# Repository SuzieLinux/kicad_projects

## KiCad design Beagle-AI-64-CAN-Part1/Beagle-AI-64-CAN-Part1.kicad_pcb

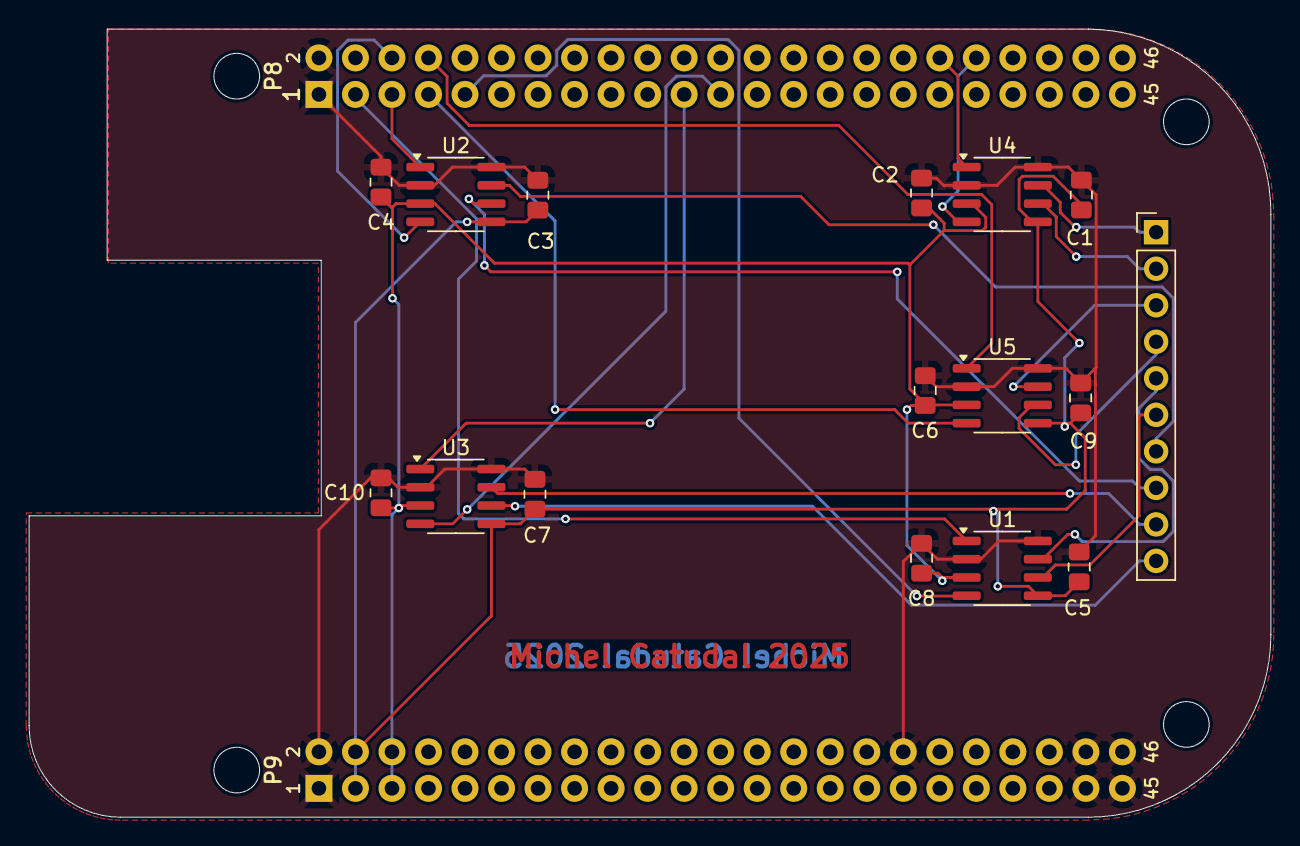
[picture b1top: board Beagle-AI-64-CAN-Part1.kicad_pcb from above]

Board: 2 copper layers, 86.4 x 54.8 mm, 17 parts (0 on the bottom side), 23 nets.

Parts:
C1, C2, C3, C4, C5, C6, C7, C8, C9, C10: 0.1uF; C_0805_2012Metric_Pad1.18x1.45mm_HandSolder
J17: Beaglebone_AI64; BEAGLE_BONE_BLACK_CAPE
P1: CAN group; PinHeader_1x10_P2.54mm_Vertical
U1, U2, U3, U4, U5: MCP2562; SOIC-8_3.9x4.9mm_P1.27mm

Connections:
+3.3V: C1.2, C3.2, C5.2, C7.2, C9.2, J17.P9.3 (VSYS_IO_3V3), J17.P9.4 (VSYS_IO_3V3), U1.5 (Vio), U2.5 (Vio), U3.5 (Vio), U4.5 (Vio), U5.5 (Vio)
+5V: C2.1, C4.1, C6.1, C8.1, C10.1, J17.P9.5 (DC_VDD_5V), J17.P9.6 (DC_VDD_5V), U1.3 (VDD), U2.3 (VDD), U3.3 (VDD), U4.3 (VDD), U5.3 (VDD)
/CAN4H: P1.1, U4.7 (CANH)
/CAN4L: P1.2, U4.6 (CANL)
/CAN5H: P1.3, U5.7 (CANH)
/CAN5L: P1.4, U5.6 (CANL)
/CAN6H: P1.5, U1.7 (CANH)
/CAN6L: P1.6, U1.6 (CANL)
/CAN7H: P1.7, U2.7 (CANH)
/CAN7L: P1.8, U2.6 (CANL)
/CAN8H: P1.9, U3.7 (CANH)
/CAN8L: P1.10, U3.6 (CANL)
GND: C1.1, C2.2, C3.1, C4.2, C5.1, C6.2, C7.1, C8.2, C9.1, C10.2, J17.P8.1 (GND), J17.P8.2 (GND), J17.P9.1 (GND), J17.P9.2 (GND), J17.P9.34 (GND), J17.P9.43 (GND), J17.P9.44 (GND), J17.P9.45 (GND), J17.P9.46 (GND), U1.2 (VSS), U1.8 (STBY), U2.2 (VSS), U2.8 (STBY), U3.2 (VSS), U3.8 (STBY), U4.2 (VSS), U4.8 (STBY), U5.2 (VSS), U5.8 (STBY)
unnamed: J17.P8.23 (AB23_MCAN8_RX), U3.4 (RXD)
unnamed: J17.P8.7 (AD24_MCAN5_RX), U5.4 (RXD)
unnamed: J17.P8.36 (AE20_MCAN4_TX), U4.1 (TXD)
unnamed: J17.P8.9 (AE24_MCAN6_RX), U1.4 (RXD)
unnamed: J17.P8.21 (AF21_MCAN8_TX), U3.1 (TXD)
unnamed: J17.P8.8 (AG24_MCAN5_TX), U5.1 (TXD)
unnamed: J17.P8.6 (AG25_MCAN7_RX), U2.4 (RXD)
unnamed: J17.P8.3 (AH21_MCAN6_TX), U1.1 (TXD)
unnamed: J17.P8.5 (AH25_MCAN7_TX), U2.1 (TXD)
unnamed: J17.P8.38 (Y29_AJ20), U4.4 (RXD)

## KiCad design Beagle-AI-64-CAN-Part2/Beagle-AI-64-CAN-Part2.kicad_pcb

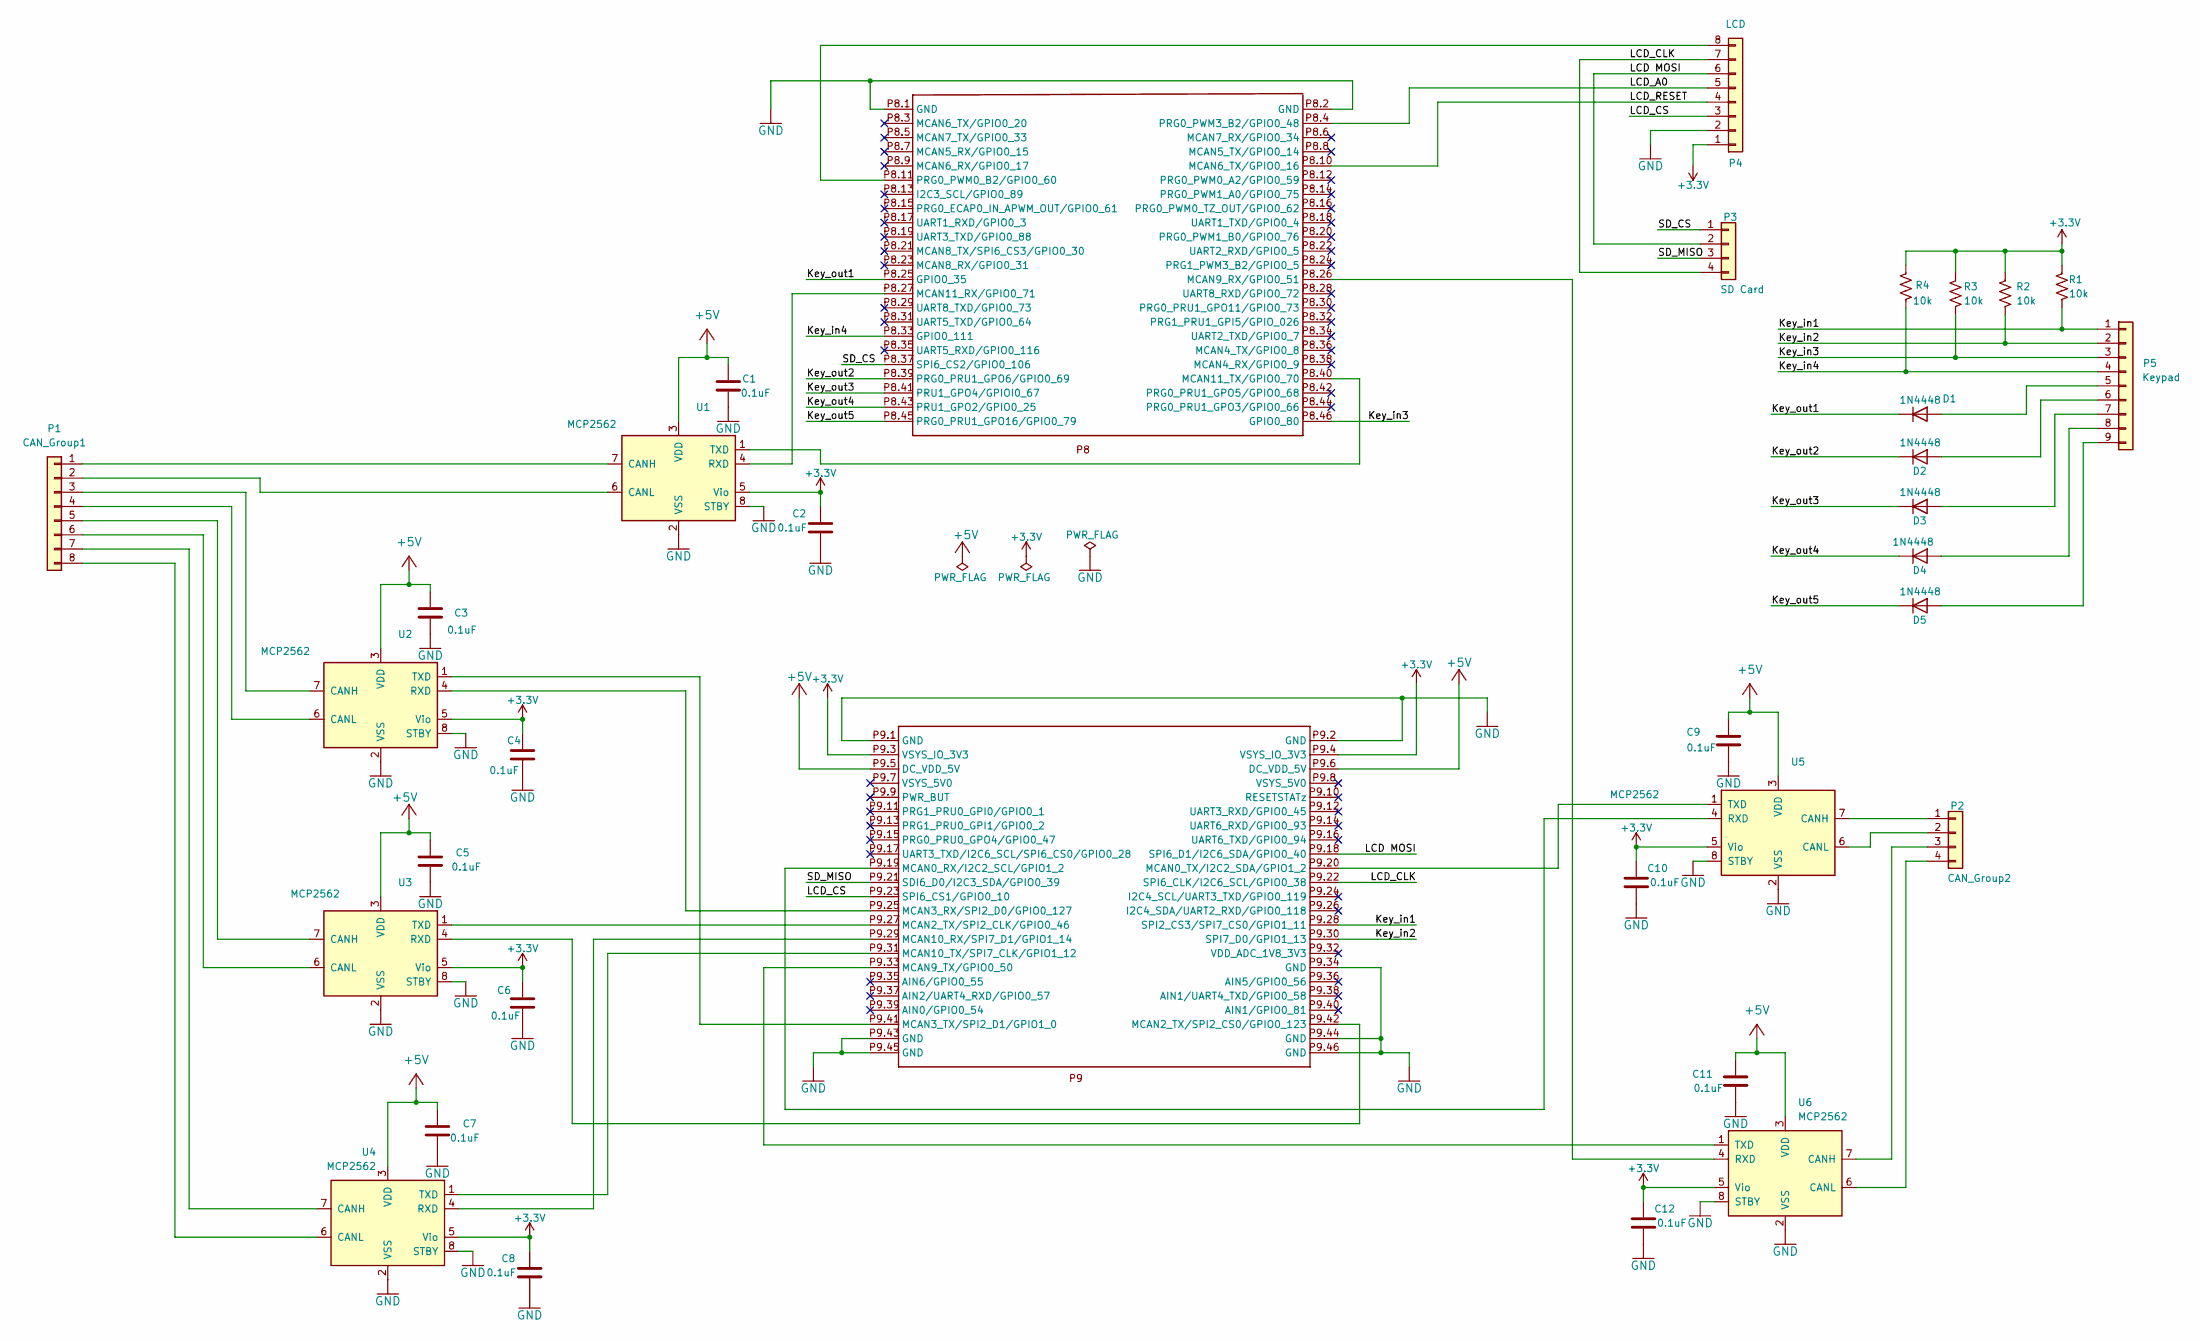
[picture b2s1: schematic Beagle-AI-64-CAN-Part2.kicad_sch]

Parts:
C1, C2, C3, C4, C5, C6, C7, C8, C9, C10, C11, C12: 0.1uF; C_0805_2012Metric_Pad1.18x1.45mm_HandSolder
D1, D2, D3, D4, D5: 1N4448; D_DO-35_SOD27_P7.62mm_Horizontal
J17: Beaglebone_AI64; BEAGLE_BONE_BLACK_CAPE
P1: CAN_Group1; PinHeader_1x08_P2.54mm_Vertical
P2: CAN_Group2; PinHeader_1x04_P2.54mm_Vertical
P3: SD Card; PinHeader_1x04_P2.54mm_Vertical
P4: LCD; PinHeader_1x08_P2.54mm_Vertical
P5: Keypad; PinHeader_1x09_P2.54mm_Vertical
R1, R2, R3, R4: 10k; R_0805_2012Metric
U1, U2, U3, U4, U5, U6: MCP2562; SOIC-8_3.9x4.9mm_P1.27mm

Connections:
+3.3V: C2.2, C4.2, C6.2, C8.2, C10.2, C12.2, J17.P9.3 (VSYS_IO_3V3), J17.P9.4 (VSYS_IO_3V3), P4.1, R1.1, R2.1, R3.1, R4.1, U1.5 (Vio), U2.5 (Vio), U3.5 (Vio), U4.5 (Vio), U5.5 (Vio), U6.5 (Vio)
+5V: C1.1, C3.1, C5.1, C7.1, C9.1, C11.1, J17.P9.5 (DC_VDD_5V), J17.P9.6 (DC_VDD_5V), U1.3 (VDD), U2.3 (VDD), U3.3 (VDD), U4.3 (VDD), U5.3 (VDD), U6.3 (VDD)
/Key_in1: J17.P9.28 (SPI2_CS3/SPI7_CS0/GPIO1_11), P5.1, R1.2
/Key_in2: J17.P9.30 (SPI7_D0/GPIO1_13), P5.2, R2.2
/Key_in3: J17.P8.46 (GPIO0_80), P5.3, R3.2
/Key_in4: J17.P8.33 (GPIO0_111), P5.4, R4.2
/Key_out1: D1.1 (K), J17.P8.25 (GPIO0_35)
/Key_out2: D2.1 (K), J17.P8.39 (PRG0_PRU1_GPO6/GPIO0_69)
/Key_out3: D3.1 (K), J17.P8.41 (PRU1_GPO4/GPIOI0_67)
/Key_out4: D4.1 (K), J17.P8.43 (PRU1_GPO2/GPIO0_25)
/Key_out5: D5.1 (K), J17.P8.45 (PRG0_PRU1_GPO16/GPIO0_79)
/LCD MOSI: J17.P9.18 (SPI6_D1/I2C6_SDA/GPIO0_40), P3.2, P4.6
/LCD_A0: J17.P8.4 (PRG0_PWM3_B2/GPIO0_48), P4.5
/LCD_CLK: J17.P9.22 (SPI6_CLK/I2C6_SCL/GPIO0_38), P3.4, P4.7
/LCD_CS: J17.P9.23 (SPI6_CS1/GPIO0_10), P4.3
/LCD_RESET: J17.P8.10 (MCAN6_TX/GPIO0_16), P4.4
/SD_CS: J17.P8.37 (SPI6_CS2/GPIO0_106), P3.1
/SD_MISO: J17.P9.21 (SDI6_D0/I2C3_SDA/GPIO0_39), P3.3
GND: C1.2, C2.1, C3.2, C4.1, C5.2, C6.1, C7.2, C8.1, C9.2, C10.1, C11.2, C12.1, J17.P8.1 (GND), J17.P8.2 (GND), J17.P9.1 (GND), J17.P9.2 (GND), J17.P9.34 (GND), J17.P9.43 (GND), J17.P9.44 (GND), J17.P9.45 (GND), J17.P9.46 (GND), P4.2, U1.2 (VSS), U1.8 (STBY), U2.2 (VSS), U2.8 (STBY), U3.2 (VSS), U3.8 (STBY), U4.2 (VSS), U4.8 (STBY), U5.2 (VSS), U5.8 (STBY), U6.2 (VSS), U6.8 (STBY)
unnamed: D1.2 (A), P5.5
unnamed: D2.2 (A), P5.6
unnamed: D3.2 (A), P5.7
unnamed: D4.2 (A), P5.8
unnamed: D5.2 (A), P5.9
unnamed: J17.P8.26 (MCAN9_RX/GPIO0_51), U6.4 (RXD)
unnamed: J17.P8.27 (MCAN11_RX/GPIO0_71), U1.4 (RXD)
unnamed: J17.P8.40 (MCAN11_TX/GPIO0_70), U1.1 (TXD)
unnamed: J17.P8.11 (PRG0_PWM0_B2/GPIO0_60), P4.8
unnamed: J17.P9.19 (MCAN0_RX/I2C2_SCL/GPIO1_2), U5.4 (RXD)
unnamed: J17.P9.20 (MCAN0_TX/I2C2_SDA/GPIO1_2), U5.1 (TXD)
unnamed: J17.P9.27 (MCAN2_TX/SPI2_CLK/GPIO0_46), U3.1 (TXD)
unnamed: J17.P9.42 (MCAN2_TX/SPI2_CS0/GPIO0_123), U3.4 (RXD)
unnamed: J17.P9.25 (MCAN3_RX/SPI2_D0/GPIO0_127), U2.4 (RXD)
unnamed: J17.P9.41 (MCAN3_TX/SPI2_D1/GPIO1_0), U2.1 (TXD)
unnamed: J17.P9.33 (MCAN9_TX/GPIO0_50), U6.1 (TXD)
unnamed: J17.P9.29 (MCAN10_RX/SPI7_D1/GPIO1_14), U4.4 (RXD)
unnamed: J17.P9.31 (MCAN10_TX/SPI7_CLK/GPIO1_12), U4.1 (TXD)
unnamed: P1.1, U1.7 (CANH)
unnamed: P1.2, U1.6 (CANL)
unnamed: P1.3, U2.7 (CANH)
unnamed: P1.4, U2.6 (CANL)
unnamed: P1.5, U3.7 (CANH)
unnamed: P1.6, U3.6 (CANL)
unnamed: P1.7, U4.7 (CANH)
unnamed: P1.8, U4.6 (CANL)
unnamed: P2.1, U5.7 (CANH)
unnamed: P2.2, U5.6 (CANL)
unnamed: P2.3, U6.7 (CANH)
unnamed: P2.4, U6.6 (CANL)

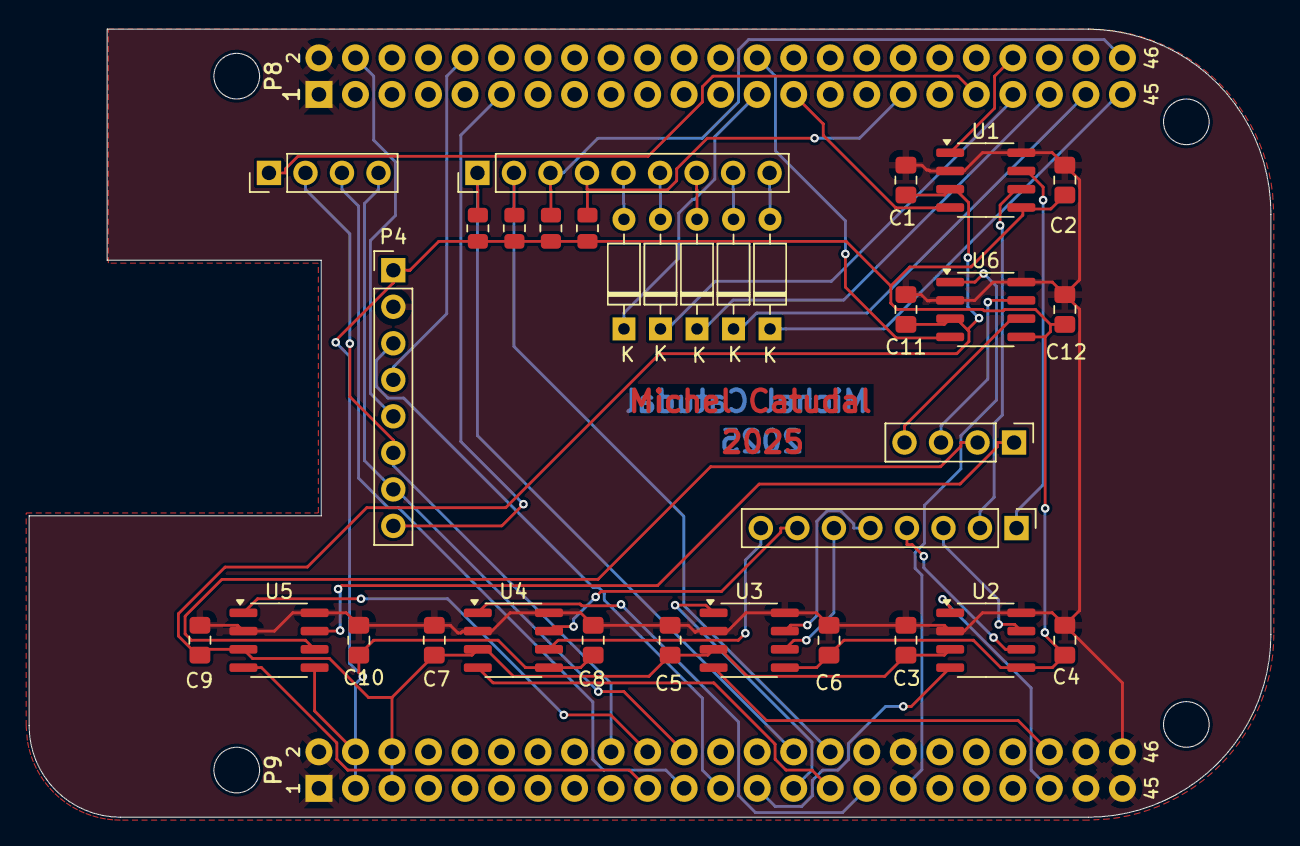
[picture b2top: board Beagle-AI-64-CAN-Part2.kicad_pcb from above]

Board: 2 copper layers, 86.4 x 54.8 mm, 33 parts (0 on the bottom side), 49 nets.

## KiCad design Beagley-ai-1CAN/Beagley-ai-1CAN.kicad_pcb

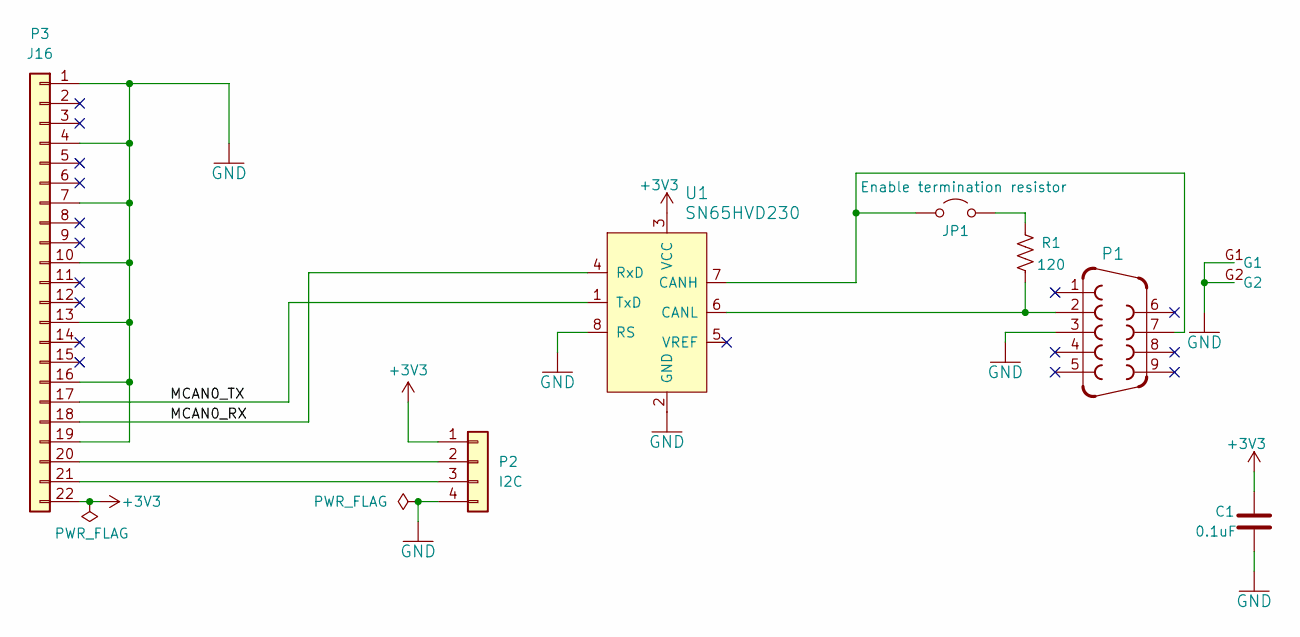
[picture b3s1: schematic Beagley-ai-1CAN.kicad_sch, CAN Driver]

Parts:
C1: 0.1uF; C_0805_2012Metric_Pad1.18x1.45mm_HandSolder
JP1: Enable termination resistor; PinHeader_1x02_P2.54mm_Vertical
P1: F09HP
P2: I2C; PinHeader_1x04_P2.00mm_Vertical
P3: J16; PinHeader_2x11_P2.54mm_reverse
R1: 120; R_2512_6332Metric_Pad1.40x3.35mm_HandSolder
U1: SN65HVD230; SOIC-8_3.9x4.9mm_P1.27mm; MPN SN65HVD230

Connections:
+3V3: C1.1, P2.1, P3.22, U1.3 (VCC)
/MCAN0_RX: P3.18, U1.4 (RxD)
/MCAN0_TX: P3.17, U1.1 (TxD)
GND: C1.2, P1.3, P1.G1, P1.G2, P2.4, P3.1, P3.4, P3.7, P3.10, P3.13, P3.16, P3.19, U1.2 (GND), U1.8 (RS)
unnamed: JP1.1 (A), P1.7, U1.7 (CANH)
unnamed: JP1.2 (B), R1.1
unnamed: P2.2, P3.20
unnamed: P2.3, P3.21
unnamed: P1.2, R1.2, U1.6 (CANL)

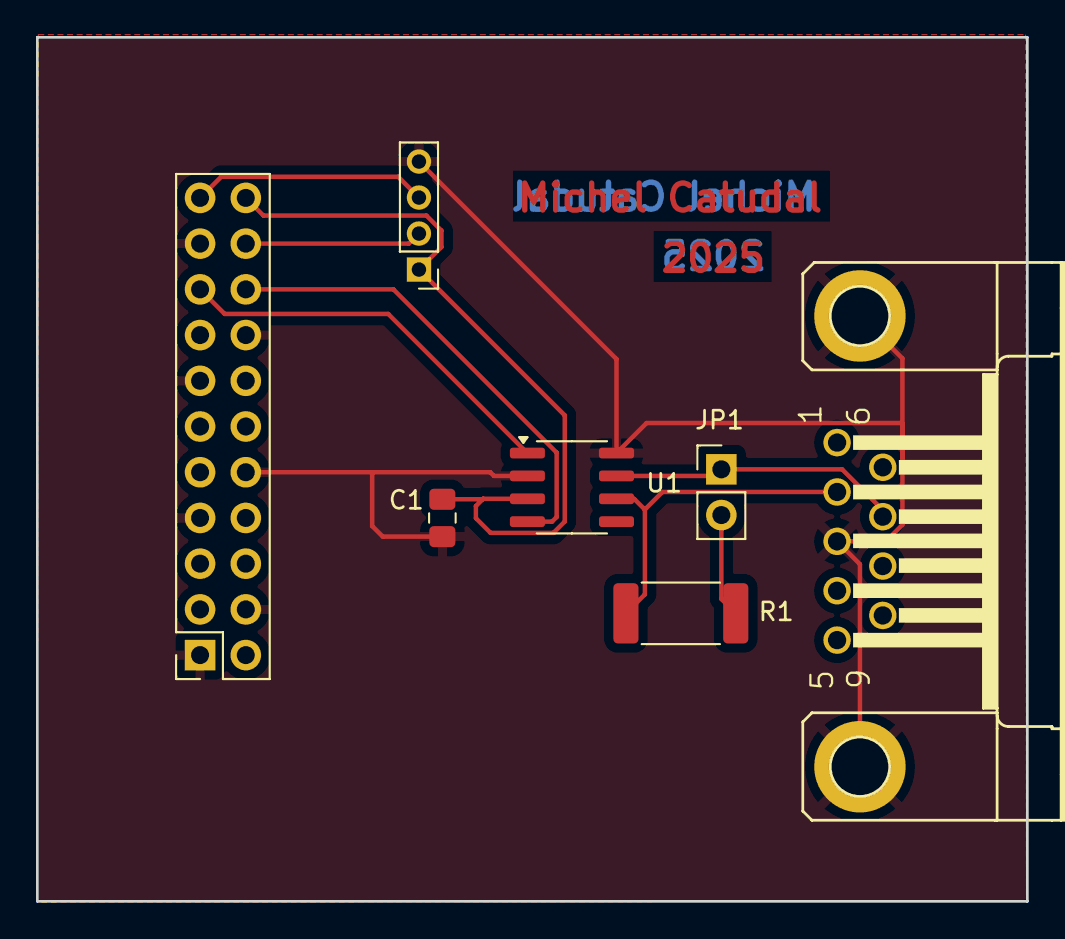
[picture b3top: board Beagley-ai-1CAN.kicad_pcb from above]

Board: 2 copper layers, 55.0 x 48.0 mm, 7 parts (0 on the bottom side), 9 nets.

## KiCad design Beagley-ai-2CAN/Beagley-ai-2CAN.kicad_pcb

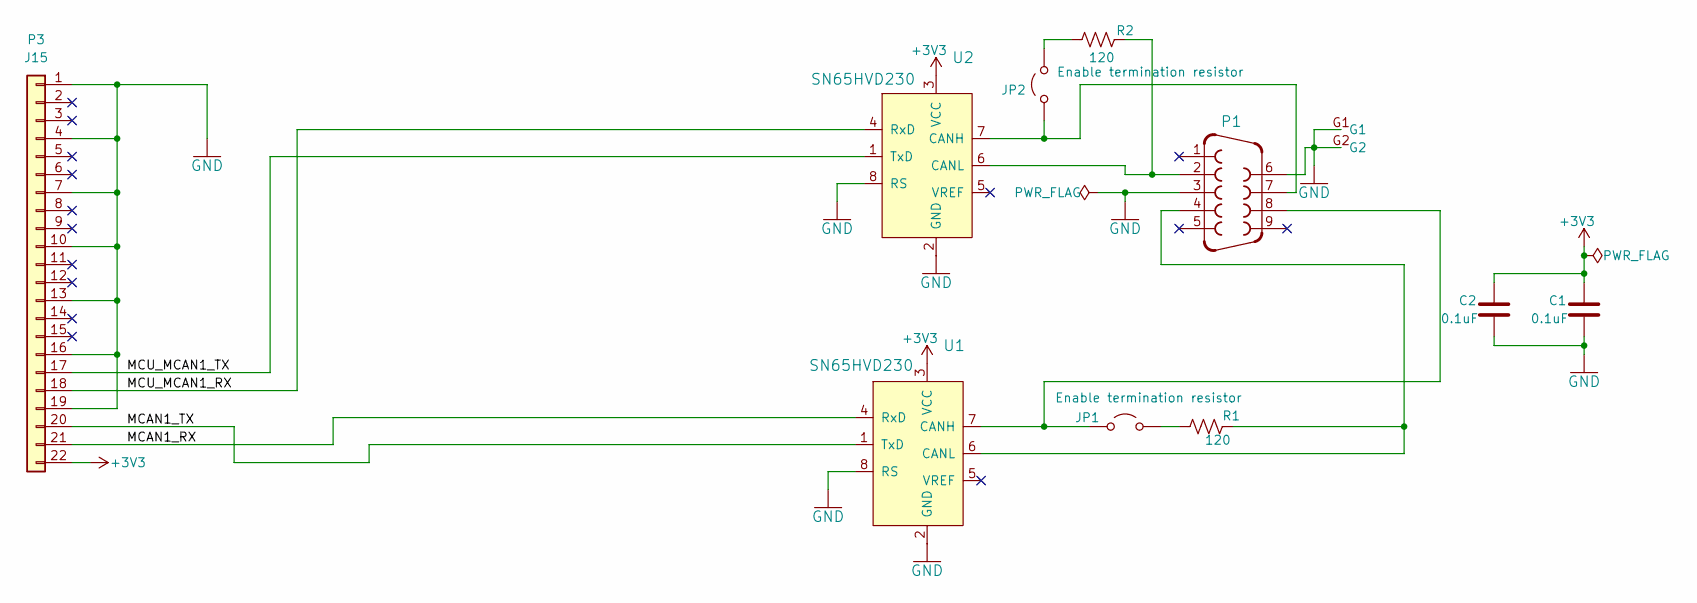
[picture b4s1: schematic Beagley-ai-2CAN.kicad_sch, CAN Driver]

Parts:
C1, C2: 0.1uF; C_0805_2012Metric_Pad1.18x1.45mm_HandSolder
JP1, JP2: Enable termination resistor; PinHeader_1x02_P2.54mm_Vertical
P1: F09HP
P3: J15; PinHeader_2x11_P2.54mm_reverse
R1, R2: 120; R_2512_6332Metric_Pad1.40x3.35mm_HandSolder
U1, U2: SN65HVD230; SOIC-8_3.9x4.9mm_P1.27mm; MPN SN65HVD230

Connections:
+3V3: C1.1, C2.1, P3.22, U1.3 (VCC), U2.3 (VCC)
/MCAN1_RX: P3.21, U1.4 (RxD)
/MCAN1_TX: P3.20, U1.1 (TxD)
/MCU_MCAN1_RX: P3.18, U2.4 (RxD)
/MCU_MCAN1_TX: P3.17, U2.1 (TxD)
GND: C1.2, C2.2, P1.3, P1.6, P1.G1, P1.G2, P3.1, P3.4, P3.7, P3.10, P3.13, P3.16, P3.19, U1.2 (GND), U1.8 (RS), U2.2 (GND), U2.8 (RS)
unnamed: JP1.1 (A), P1.8, U1.7 (CANH)
unnamed: JP1.2 (B), R1.1
unnamed: JP2.1 (A), P1.7, U2.7 (CANH)
unnamed: JP2.2 (B), R2.1
unnamed: P1.4, R1.2, U1.6 (CANL)
unnamed: P1.2, R2.2, U2.6 (CANL)

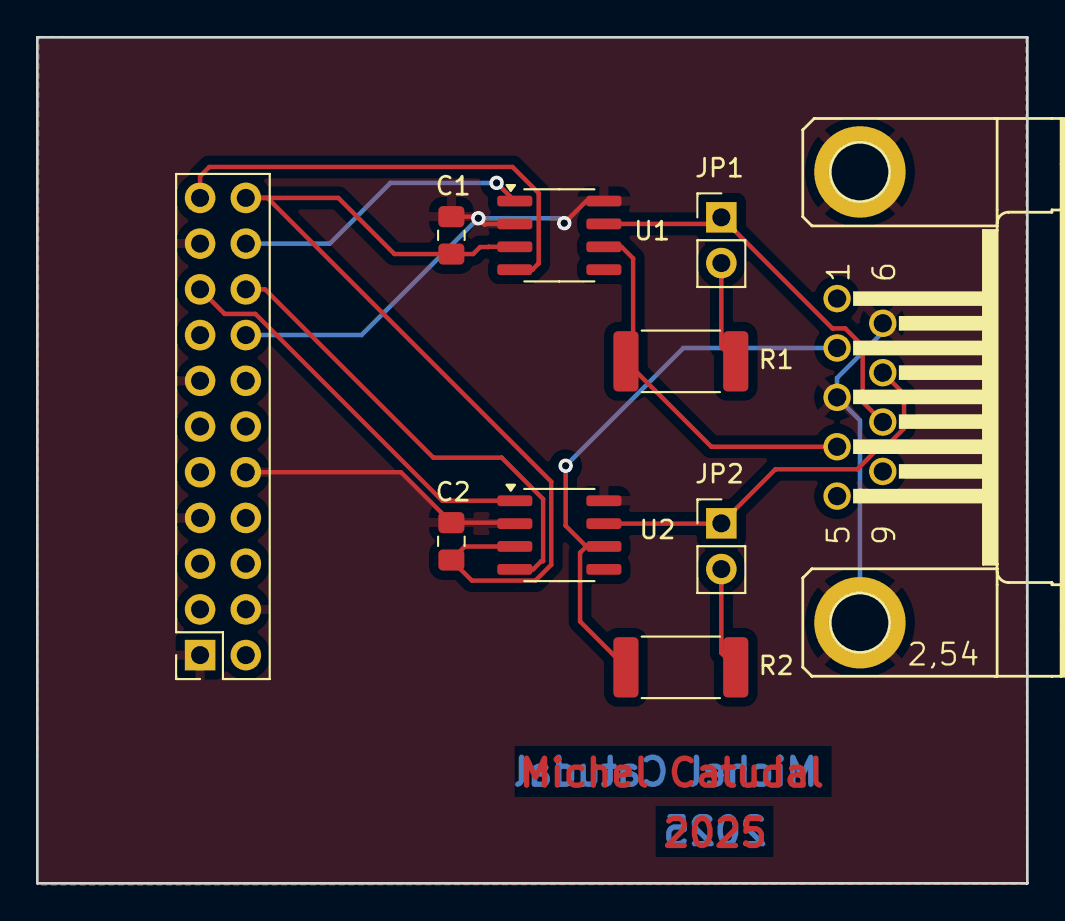
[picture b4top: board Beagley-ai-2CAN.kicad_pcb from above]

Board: 2 copper layers, 55.0 x 47.0 mm, 10 parts (0 on the bottom side), 12 nets.

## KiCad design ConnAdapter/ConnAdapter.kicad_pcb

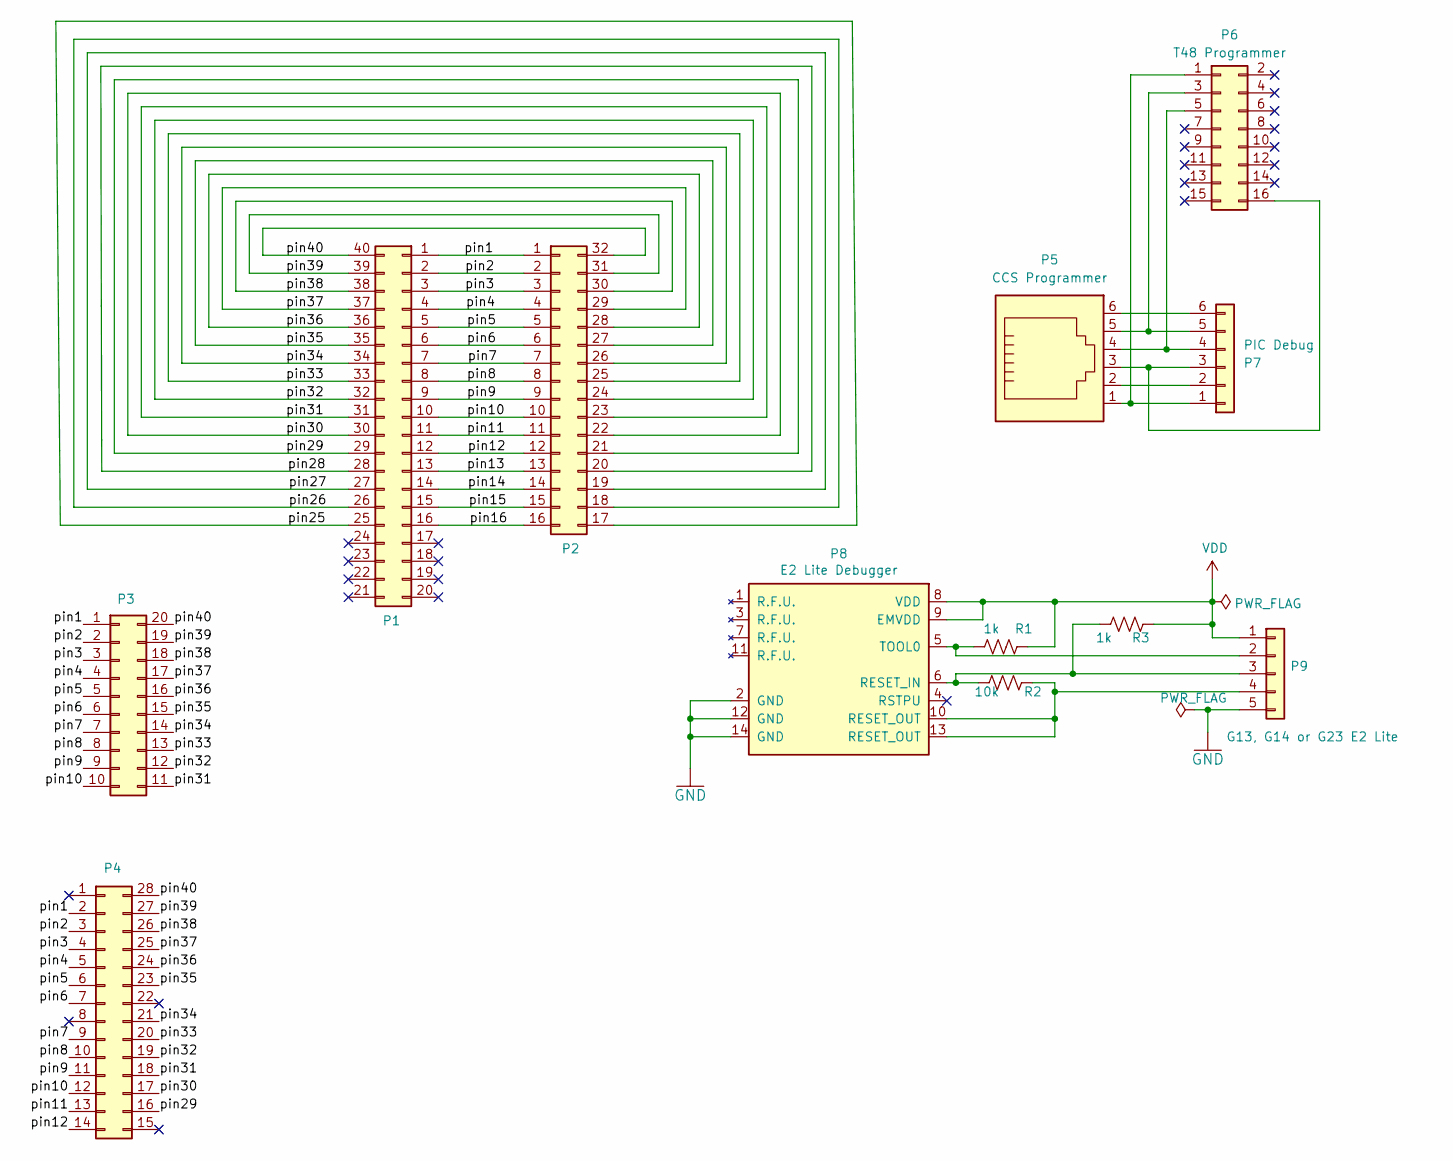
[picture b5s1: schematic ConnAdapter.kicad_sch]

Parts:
P1: Conn_02x20_Counter_Clockwise; DIP-40_W25.4mm_LongPads
P2: Conn_02x16_Counter_Clockwise; PLCC-32_THT-Socket
P3: Conn_02x10_Counter_Clockwise; PLCC-20_THT-Socket
P4: Conn_02x14_Counter_Clockwise; PLCC-28_THT-Socket
P5: CCS Programmer; RJ12_Amphenol_54601-x06_Horizontal
P6: T48 Programmer; XGecu_16pins
P7: PIC Debug; PinSocket_1x06_P2.54mm_Vertical
P8: E2 Lite Debugger; IDC-Header_2x07_P2.54mm_Vertical
P9: G13, G14 or G23 E2 Lite; PinHeader_1x05_P2.54mm_Vertical
R1, R3: 1k; R_Axial_DIN0414_L11.9mm_D4.5mm_P15.24mm_Horizontal
R2: 10k; R_Axial_DIN0414_L11.9mm_D4.5mm_P15.24mm_Horizontal

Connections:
/pin1: P1.1, P2.1, P3.1, P4.2
/pin2: P1.2, P2.2, P3.2, P4.3
/pin3: P1.3, P2.3, P3.3, P4.4
/pin4: P1.4, P2.4, P3.4, P4.5
/pin5: P1.5, P2.5, P3.5, P4.6
/pin6: P1.6, P2.6, P3.6, P4.7
/pin7: P1.7, P2.7, P3.7, P4.9
/pin8: P1.8, P2.8, P3.8, P4.10
/pin9: P1.9, P2.9, P3.9, P4.11
/pin10: P1.10, P2.10, P3.10, P4.12
/pin11: P1.11, P2.11, P4.13
/pin12: P1.12, P2.12, P4.14
/pin13: P1.13, P2.13
/pin14: P1.14, P2.14
/pin15: P1.15, P2.15
/pin16: P1.16, P2.16
/pin25: P1.25, P2.17
/pin26: P1.26, P2.18
/pin27: P1.27, P2.19
/pin28: P1.28, P2.20
/pin29: P1.29, P2.21, P4.16
/pin30: P1.30, P2.22, P4.17
/pin31: P1.31, P2.23, P3.11, P4.18
/pin32: P1.32, P2.24, P3.12, P4.19
/pin33: P1.33, P2.25, P3.13, P4.20
/pin34: P1.34, P2.26, P3.14, P4.21
/pin35: P1.35, P2.27, P3.15, P4.23
/pin36: P1.36, P2.28, P3.16, P4.24
/pin37: P1.37, P2.29, P3.17, P4.25
/pin38: P1.38, P2.30, P3.18, P4.26
/pin39: P1.39, P2.31, P3.19, P4.27
/pin40: P1.40, P2.32, P3.20, P4.28
GND: P8.2 (GND), P8.12 (GND), P8.14 (GND), P9.5
unnamed: P5.1, P6.1, P7.1
unnamed: P5.5, P6.3, P7.5
unnamed: P5.4, P6.5, P7.4
unnamed: P5.3, P6.16, P7.3
unnamed: P5.2, P7.2
unnamed: P5.6, P7.6
unnamed: P8.6 (RESET_IN), P9.3, R2.2, R3.2
unnamed: P8.5 (TOOL0), P9.2, R1.2
unnamed: P8.10 (RESET_OUT), P8.13 (RESET_OUT), P9.4, R2.1
VDD: P8.8 (VDD), P8.9 (EMVDD), P9.1, R1.1, R3.1

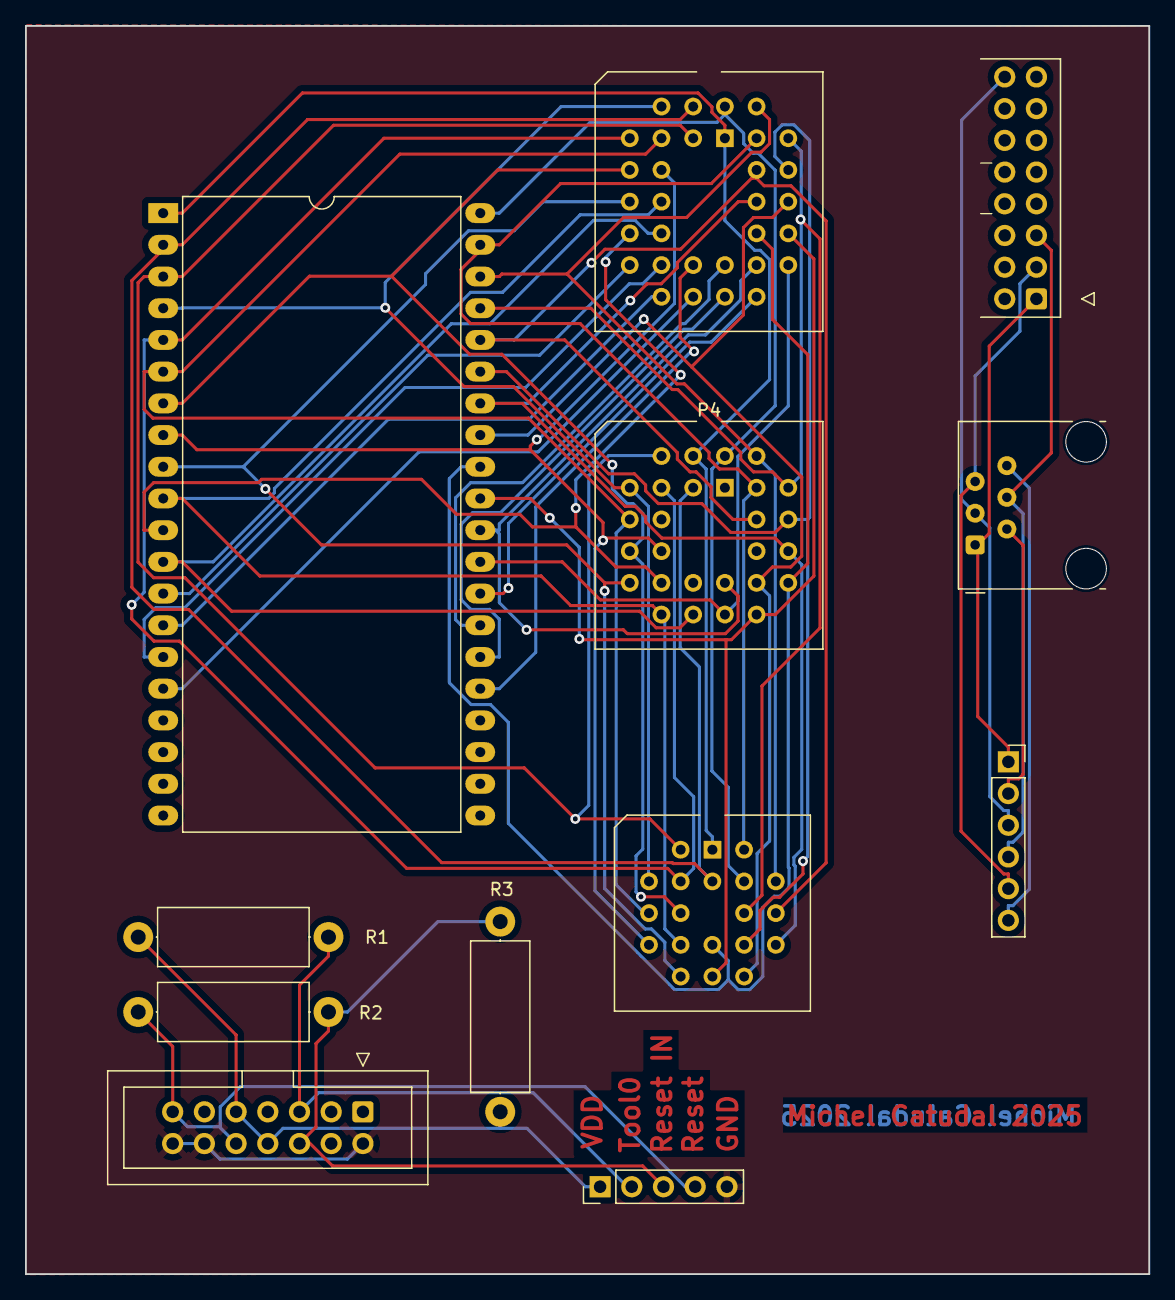
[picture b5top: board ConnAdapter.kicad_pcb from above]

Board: 2 copper layers, 90.0 x 100.0 mm, 12 parts (0 on the bottom side), 43 nets.

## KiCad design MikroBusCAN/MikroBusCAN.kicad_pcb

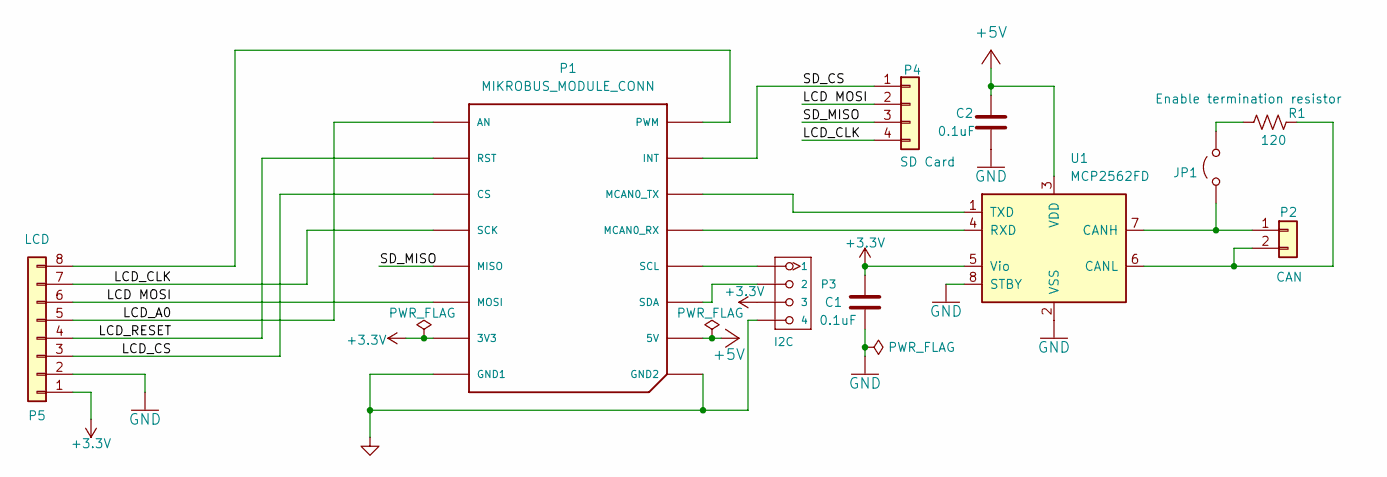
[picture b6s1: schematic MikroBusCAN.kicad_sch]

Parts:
C1, C2: 0.1uF; C_Disc_D5.0mm_W2.5mm_P5.00mm
JP1: Enable termination resistor; PinHeader_1x02_P2.54mm_Vertical
P1: MIKROBUS_MODULE_CONN
P2: CAN; PinHeader_1x02_P2.54mm_Vertical
P3: I2C; NS-Tech_Grove_1x04_P2mm_Vertical
P4: SD Card; PinHeader_1x04_P2.54mm_Vertical
P5: LCD; PinHeader_1x08_P2.54mm_Vertical
R1: 120; R_Axial_DIN0309_L9.0mm_D3.2mm_P15.24mm_Horizontal
U1: MCP2562FD; CERDIP-8_W7.62mm_SideBrazed_LongPads

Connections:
+3.3V: C1.2, P1.P7 (3V3), P3.3, P5.1, U1.5 (Vio)
+5V: C2.1, P1.P10 (5V), U1.3 (VDD)
/LCD MOSI: P1.P6 (MOSI), P4.2, P5.6
/LCD_A0: P1.P1 (AN), P5.5
/LCD_CLK: P1.P4 (SCK), P4.4, P5.7
/LCD_CS: P1.P3 (CS), P5.3
/LCD_RESET: P1.P2 (RST), P5.4
/SD_CS: P1.P15 (INT), P4.1
/SD_MISO: P1.P5 (MISO), P4.3
GND: C1.1, C2.2, P1.P8 (GND1), P1.P9 (GND2), P3.4, P5.2, U1.2 (VSS), U1.8 (STBY)
unnamed: JP1.1 (A), P2.1, U1.7 (CANH)
unnamed: JP1.2 (B), R1.1
unnamed: P1.P13 (MCAN0_RX), U1.4 (RXD)
unnamed: P1.P14 (MCAN0_TX), U1.1 (TXD)
unnamed: P1.P16 (PWM), P5.8
unnamed: P1.P12 (SCL), P3.1
unnamed: P1.P11 (SDA), P3.2
unnamed: P2.2, R1.2, U1.6 (CANL)

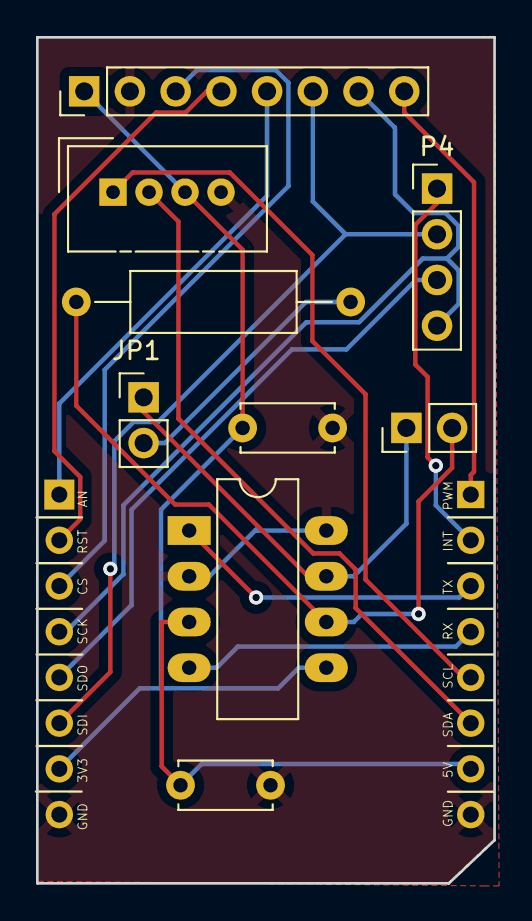
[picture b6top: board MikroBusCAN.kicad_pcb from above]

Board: 2 copper layers, 25.4 x 47.0 mm, 10 parts (0 on the bottom side), 18 nets.
